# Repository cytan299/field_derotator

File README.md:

# A Field DeRotator for Alt-Az Mounted Telescopes Used for Astrophotography

by C.Y. Tan 2015

Most telescopes used for astrophotography are equatorially
mounted. However, the more popular computer controlled telescopes are
alt-az mounted and are usually deemed unsuitable for
astrophotography. The reason is that alt-az mounted telescopes have
one more degree of freedom that is not corrected because it does not
affect visual observations of celestial objects. Unfortunately, by
leaving it uncorrected, alt-az telescopes cannot be used for long
exposure astrophotography. In order to overcome this flaw in alt-az
mounted telescopes, I have designed and built a field derotator that
removes this degree of freedom and thus allows alt-az telescopes to
become astrophotography platforms.

## Goal

I have built a fully functional field derotator that consists of both
a mechanical derotator and an Arduino based controller for the
LX200. All hardware, drawings, schematics, software and documentation
are open source with the respective licenses described below.

I hope that this device will be useful for astrophotographers who find
polar mounts a real pain in the rear to use, and prefer alt-az mounts
instead.

## IMPORTANT!

Field derotation **cannot** work without an off-axis guider. If you
don't plan on investing in an off-axis guider, don't bother building
this device because field derotation will not work without it.  See
[field_derotator_formula.pdf](field_derotator_formula/field_derotator_formula.pdf)
for the explanation.

## MAC OS X Frontend Executable

A compiled app bundle for the Mac can be downloaded from the
[releases repository](https://github.com/cytan299/field_derotator/releases).

## Support

All the software have been successfully compiled on Mac OS X 10.10.5
(Yosemite).

I don't do Windows or Linux so, I cannot answer questions for these
two platforms.

This is unsupported software and hardware. Build at your own peril! :)

You can submit questions or bug reports using the
[issues](https://github.com/cytan299/field_derotator/issues) tab on
the right and then click on **NEW**.

Have fun!

## Directory structure

* **arduino** The C++ code for the arduino MEGA2560.
* **arduino_case** The case design for the field derotator controller.
* **bom** Bill of materials for 1 field derotator. I also show the
  cost for building one.
* **eagle** Eagle schematic and board files.
* **emachineshop** eMachineshop files for the derotator aluminium
shell.
* **field_derotator_formula** derivation of the derotation formula,
  analysis of how off-axis guiding is improved with derotation and
  limitation of derotation.
* **frontend** C++ code for the GUI frontend for the user to control
the derotator.
* **howto** Guides for how to assemble the derotator and the
controller.

## Other information

More information can be found in he *README.md* files in each
directory and the
[wiki](https://github.com/cytan299/field_derotator/wiki/A-Field-DeRotator-for-Alt-Az-Telescopes-Used-for-Astrophotography)
of this project on github.

## Publications

This project has been published in
[Circuit Cellar Ink](http://www.circuitcellar.com) Issues 309 (April
2016) and 310 (May 2016), titled "A Field DeRotator for
Astrophotography by C.Y. Tan" Parts 1 and 2. Details of the motivation
for building the field derotator can be found in Issue 309 and the
description of the electronic circuits, and gear ratio calculations
can be found in Issue 310.

## Copyright
All the software, documentation, hardware that I have written is
copyright 2015 C.Y. Tan.

All software is released under GPLv3

All documentation is released under Creative Commons
Attribution-ShareAlike 3.0 Unported License or GNU Free
Documentation License, Version 1.3

All hardware is released under CERN Hardware Open License v1.2

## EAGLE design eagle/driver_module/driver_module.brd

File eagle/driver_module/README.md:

# Driver Module

The driver module is mounted on the derotator that takes signals from
the controller to step the stepper motor. It also sends back an
interrupt signal when the derotator is at its *HOME* position.

## Copyright

The schematic and board designs are copyright 2015 C.Y. Tan and
released under the CERN Open Hardware License v1.2

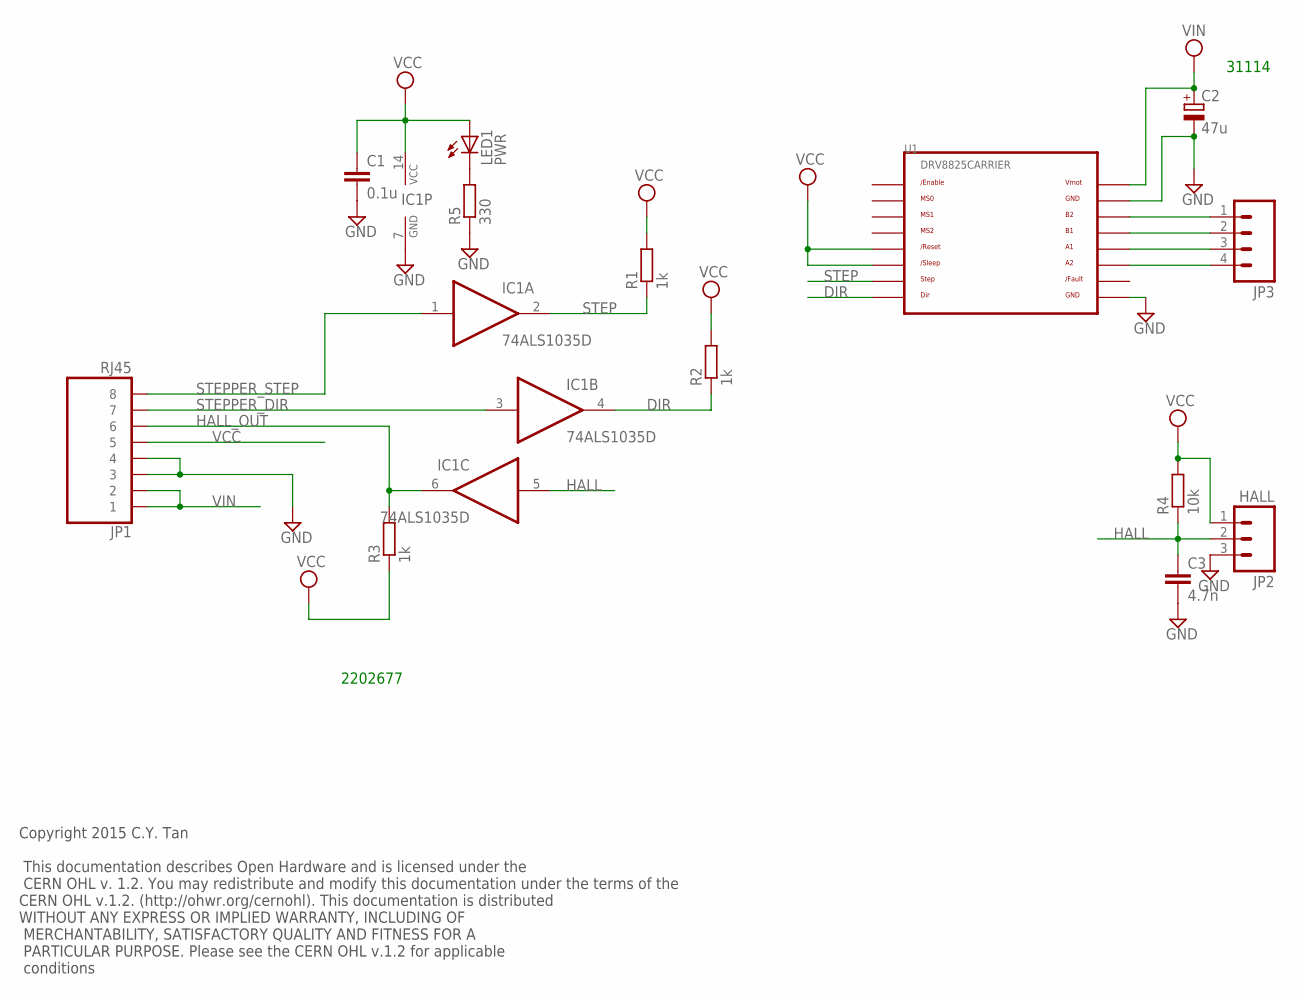
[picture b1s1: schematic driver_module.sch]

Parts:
C1: 0.1u; C1206
C2: 47u; E2,5-6
C3: 4.7n; C1206
IC1: 74ALS1035D; SO14
JP1: RJ45; RJ45-8
JP2: HALL; 1X03
JP3: M04PTH; 1X04
LED1: PWR; CHIPLED_1206
R1, R2, R3: 1k; M0805
R4: 10k; M0805
R5: 330; M0805
U1: DRV8825CARRIER

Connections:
/FAULT: U1./FAULT
DIR: IC1.4 (O), R2.1, U1.DIR
GND: C1.2, C2.-, C3.2, IC1.7 (GND), JP1.3, JP1.4, JP2.3, R5.1, U1.GND@0 (GND), U1.GND@1 (GND)
HALL: C3.1, IC1.5 (I), JP2.2, R4.1
HALL_OUT: IC1.6 (O), JP1.6, R3.2
unnamed: JP3.1, U1.B2
unnamed: JP3.2, U1.B1
unnamed: LED1.C, R5.2
unnamed: JP3.3, U1.A1
unnamed: JP3.4, U1.A2
STEP: IC1.2 (O), R1.1, U1.STEP
STEPPER_DIR: IC1.3 (I), JP1.7
STEPPER_STEP: IC1.1 (I), JP1.8
VCC: C1.1, IC1.14 (VCC), JP1.5, JP2.1, LED1.A, R1.2, R2.2, R3.1, R4.2, U1./RESET, U1./SLEEP
VIN: C2.+, JP1.1, JP1.2, U1.VMOT

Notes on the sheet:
2202677
31114
Copyright 2015 C.Y. Tan This documentation describes Open Hardware and is licensed under the CERN OHL v. 1.2. You may redistribute and modify this documentation under the terms of the CERN OHL v.1.2. (http://ohwr.org/cernohl). This documentation is distributed WITHOUT ANY EXPRESS OR IMPLIED WARRANT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

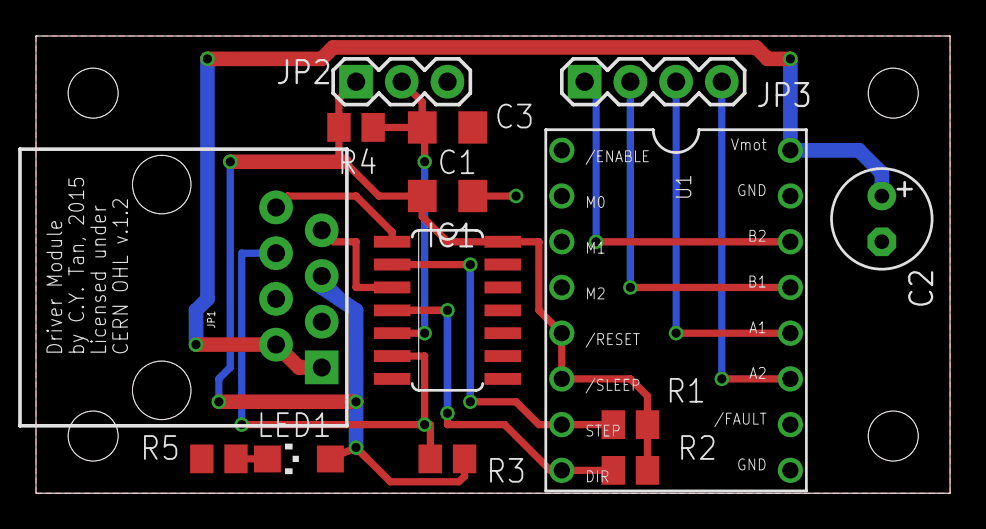
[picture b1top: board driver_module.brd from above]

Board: 2 copper layers, 50.8 x 25.4 mm, 14 parts (0 on the bottom side), 14 nets.

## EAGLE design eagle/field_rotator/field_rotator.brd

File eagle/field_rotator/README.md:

# Field Rotator Controller

This is the module that is installed in the Arduino controller that
acts as the interface between the MEGA2560 and the LX200 and the
driver_module.

## Copyright

The schematic and board designs are copyright 2015 C.Y. Tan and
released under the CERN Open Hardware License v1.2

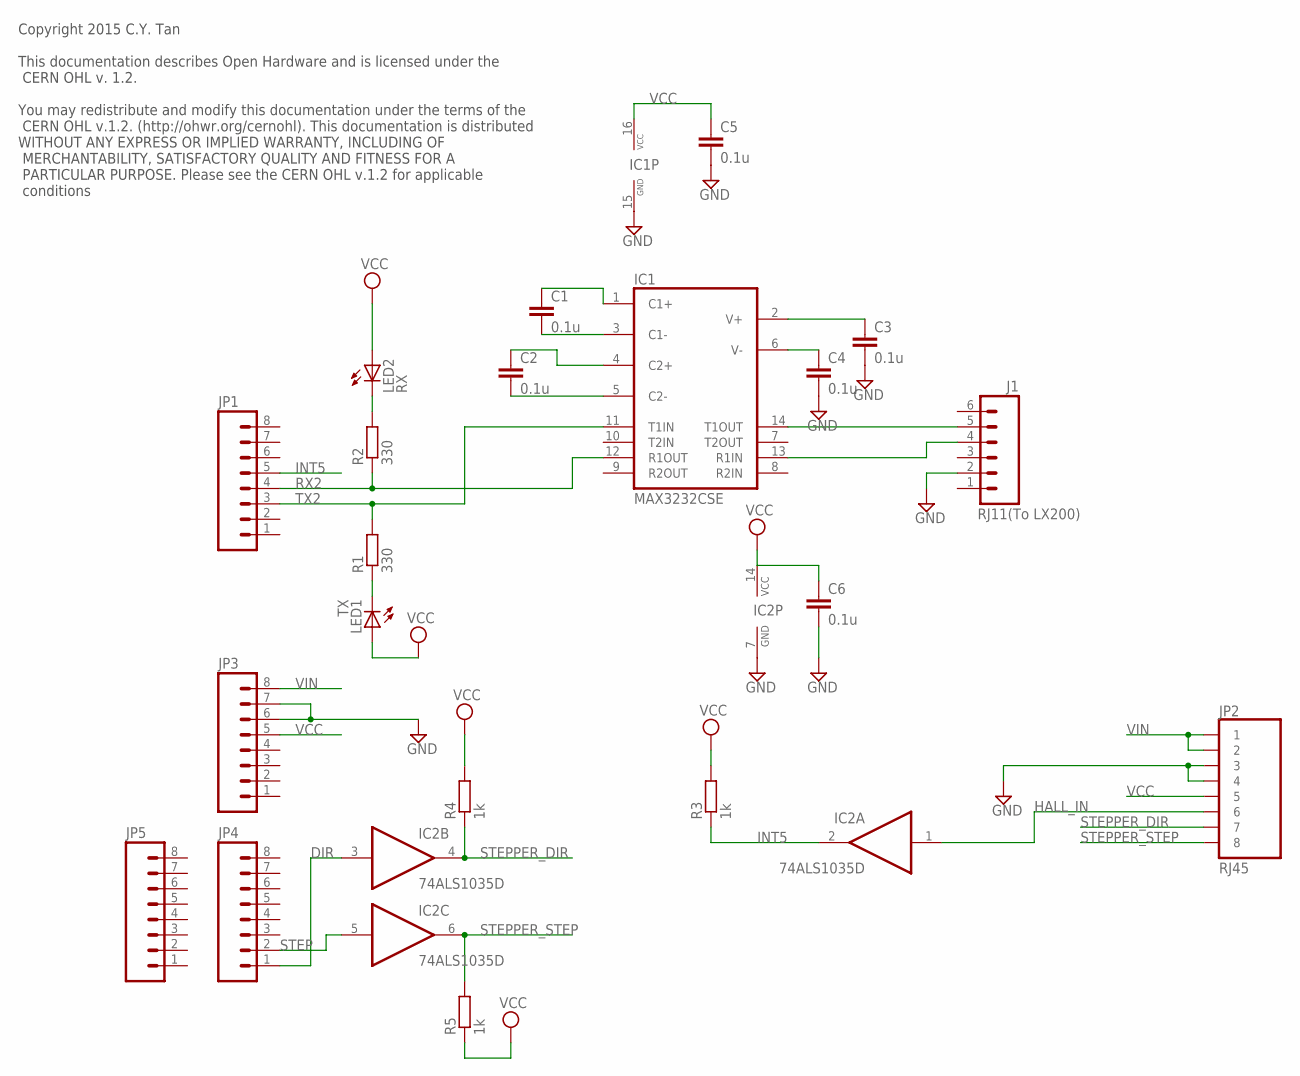
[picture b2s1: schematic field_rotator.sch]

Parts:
C1, C2, C3, C4, C5, C6: 0.1u; C1206
IC1: MAX3232CSE; SO16
IC2: 74ALS1035D; SO14
J1: RJ11(To LX200); RJ11-6
JP1, JP3, JP4, JP5: M08SILK_FEMALE_PTH; 1X08
JP2: RJ45; RJ45-8
LED1: TX; CHIPLED_1206
LED2: RX; CHIPLED_1206
R1, R2: 330; R0805
R3, R4, R5: 1k; R0805

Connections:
DIR: IC2.3 (I), JP4.1
GND: C3.2, C4.2, C5.2, C6.2, IC1.15 (GND), IC2.7 (GND), J1.2, JP2.3, JP2.4, JP3.6, JP3.7
HALL_IN: IC2.1 (I), JP2.6
INT5: IC2.2 (O), JP1.5, R3.1
unnamed: C1.1, IC1.1 (C1+)
unnamed: C1.2, IC1.3 (C1-)
unnamed: C2.1, IC1.4 (C2+)
unnamed: C2.2, IC1.5 (C2-)
unnamed: C3.1, IC1.2 (V+)
unnamed: C4.1, IC1.6 (V-)
unnamed: LED1.C, R1.1
unnamed: LED2.C, R2.2
unnamed: IC1.14 (T1OUT), J1.5
unnamed: IC1.13 (R1IN), J1.4
RX2: IC1.12 (R1OUT), JP1.4, R2.1
STEP: IC2.5 (I), JP4.2
STEPPER_DIR: IC2.4 (O), JP2.7, R4.1
STEPPER_STEP: IC2.6 (O), JP2.8, R5.2
TX2: IC1.11 (T1IN), JP1.3, R1.2
VCC: C5.1, C6.1, IC1.16 (VCC), IC2.14 (VCC), JP2.5, JP3.5, LED1.A, LED2.A, R3.2, R4.2, R5.1
VIN: JP2.1, JP2.2, JP3.8

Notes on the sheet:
Copyright 2015 C.Y. Tan This documentation describes Open Hardware and is licensed under the CERN OHL v. 1.2. You may redistribute and modify this documentation under the terms of the CERN OHL v.1.2. (http://ohwr.org/cernohl). This documentation is distributed WITHOUT ANY EXPRESS OR IMPLIED WARRANT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

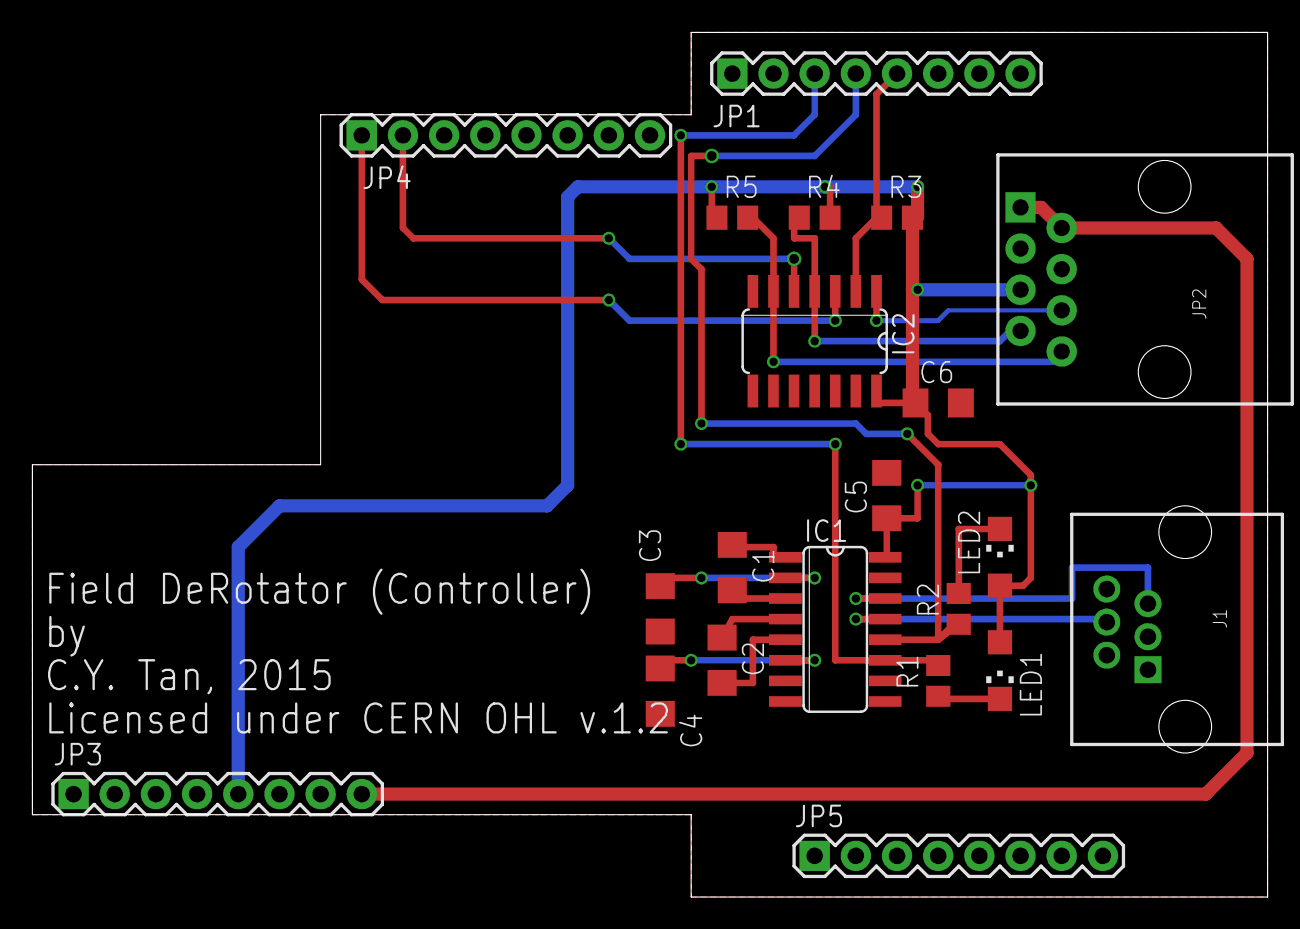
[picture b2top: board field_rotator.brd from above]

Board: 2 copper layers, 76.2 x 53.3 mm, 21 parts (0 on the bottom side), 21 nets.

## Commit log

2015-05-26 This is the base class for TCPServer and SerialServer. The main purpose is to have a common code for servicing requests.
2015-06-08 Added more commands to execute
2015-06-14 BaseServer.cpp: Enabled WLAN setup. RequestPacket.hpp: Added CMDs for setting WLAN parameters.
2015-08-02 Added GPLv3 license to all source files. Added COPYING.TXT to support GPLv3
2015-08-17 Create arduino
2015-08-17 removed arduino
2015-08-17 created arduino/derot directory
2015-08-17 Added arduino/derot
2015-08-17 removed arduino/derot
2015-08-17 Removed README.md
2015-08-17 Create BaseServer
2015-08-17 Removed BaseServer
2015-08-17 Added arduino/lib/BaseServer
2015-08-17 Added arduino/lib/DeRotator
2015-08-17 Added SerialServer
2015-08-17 Added arduino/lib/TCPServer
2015-08-17 Added arduino/lib/Telescopes
2015-08-17 Added arduino/lib/UserIO
2015-08-17 Added/frontend/derot
2015-08-18 Added bom and field derotator formula
2015-08-18 Added frontend/README.md
2015-08-18 Added howto files
2015-08-18 Added eagle files
2015-08-18 Added files to arduino_case and emachine_shop
2015-08-18 Added modified library files from Adafruit and Arduino
2015-08-18 Added a README.md to the root directory
2015-08-18 Updated arduino/README.md
2015-08-18 Updated arduino/README.md, arduino/lib/README.md
2015-08-18 Updated arduino_case/README.md
2015-08-18 Updated bom/README.md
2015-08-18 Updated eagle/README.md
2015-08-18 Updated emachineshop/README.md
2015-08-18 Updated field_derotator_formula/README.md
2015-08-18 arduino
2015-08-18 Updated arduino/README.md arduino/lib/README.md
2015-08-18 Updated howto/README.md
2015-08-18 Updated copyright in README.md
2015-08-18 Added pictures to wiki_pics
2015-08-19 Updated frontend/README.md
2015-08-19 Updated arduino/lib/README.md
2015-08-19 Updated eagle README.md's. Added pictures to wiki_pics
2015-08-19 Updated README.md and bom/README.md
2015-08-20 README.md
2015-08-20 Updated eagle/driver_module schematic
2015-08-23 Updated frontend/derotator pics
2015-08-23 Updated controller.pdf to include making of pushbutton switch button
2015-08-28 Added derotator picture to README.md
2015-08-30 frontend: Added WIFI timeout
2015-08-31 frontend: improved app icon
2015-10-11 BaseServer.cpp: In ServiceRequests(): rp->_reply is now not always set to REPLY_OK. In CMD_GET_ALTAZ_ZETA, rp->_reply is set to the derotator_continue_status.
2015-10-11 arduino/lib: Modified BaseServer, SerialServer, TCPServer, UserIO libraries so that reply_packets have a status that actually indicates the status of the derotator rather than always REPLY_OK.
2015-10-11 frontend: Modified frontend so that the user can now set the displayed camera angle to match the real camera. Internally, error messages about the status of the derotator are now shown in the log sig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
2015-10-24 arduino: Fixed problem that derotator would hang after 1 hour. Fixed a cosmetic bug in the lcd display.
2015-10-24 ReplyPacket.hpp: Changed the defines REPLY_DEROTATOR_* defines to constants that start from -100.
2015-10-24 arduino: Updated ReplyPacket.hpp: Changed the defines REPLY_DEROTATOR_* defines to constants that start from -100.
2015-10-24 frontend: Now when we lose wifi or serial connection to the derotator, there are error messages and the user can reconnect again rather than having a frontend clean exit.
2015-10-24 Added mac osx app bundle executable
2015-10-24 Removed mac osx executable and moved it to the releases directory. Updated README to reflect this.
2015-10-24 Updated README to point to the correct path to the releases directory.
2015-10-31 frontend: Fixed CW and CCW limits display bug.
2015-10-31 Updated frontend help_interface to include setting up the display camera angle.
2015-11-14 BaseServer::ServiceRequests(): In CMD_QUERY_STATE, the StatusPacket._reply now returns to the user whether hardware derotation is derotating. StatusPacket.hpp: Added define REPLY_IS_DEROTATING to sup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
2015-11-14 Updated frontend so that the graphics now reflect whether the hardware derotator is derotating on startup or when QueryHardware is called by the user. Updated arduino BaseServer so that when the user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
2015-11-15 Updated frontend to compile with fltk-1.3.x-r10866. Removed files from incorrect merge.
2015-11-28 arduino_case: Modified front cover to have larger pushbutton holes so that the cover is easier to mount with pushbuttons. Mounting holes have been changed from hexagon holes to round. Side covers: He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
2016-01-01 controller.pdf: Added instructions for adding and LED light to the controller so that the pushbuttons can be seen in the dark.
2016-04-06 README.md: Added reference to Circuit Cellar Ink publication.
2016-04-26 README.md: Fixed Circuit Cellar Ink Issue numbers.
2016-05-29 howto: Updated controller.pdf
2016-12-25 Major improvement: Added ability to tweak the Earth's rotation. This is to allow the user to improve derotation.

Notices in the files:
eagle/field_rotator/field_rotator.brd:
Licensed under CERN OHL v.1.2
parts and their libraries:
SparkFun-Connectors: Licensing: Creative Commons ShareAlike 4.0 International - https://creativecommons.org/licenses/by-sa/4.0
